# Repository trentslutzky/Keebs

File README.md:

# Keyboards

Custom split low-profile ergonomic keyboards

### Version 1

### Version 2

- in progress

https://github.com/daprice/keyswitches.pretty

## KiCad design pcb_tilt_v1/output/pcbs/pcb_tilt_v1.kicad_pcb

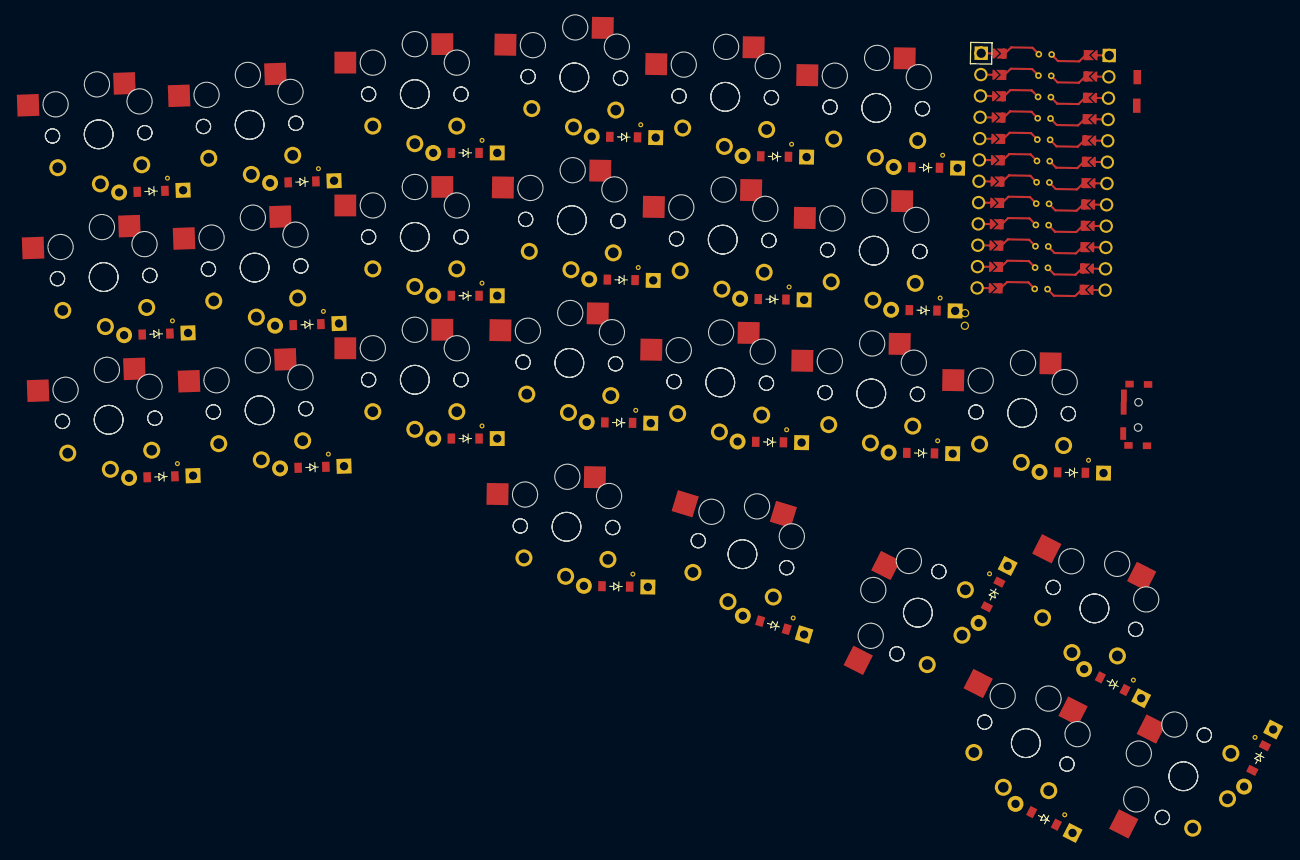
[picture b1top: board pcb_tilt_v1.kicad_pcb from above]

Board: 2 copper layers, 76 parts (0 on the bottom side), 36 nets, no tracks yet.

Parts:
D1, D2, D3, D4, D5, D6, D7, D8, D9, D10, D11, D12, D13, D14, D15, D16, D17, D18, D19, D20, D21, D22, D23, D24, D25: ComboDiode
MCU1: ProMicro
S1, S2, S3, S4, S5, S6, S7, S8, S9, S10, S11, S12, S13, S14, S15, S16, S17, S18, S19, S20, S21, S22, S23, S24, S25, S26, S27, S28, S29, S30, S31, S32, S33, S34, S35, S36, S37, S38, S39, S40, S41, S42, S43, S44, S45, S46, S47, S48, S49, S50: PG1350

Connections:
D2: D1.1, D1.2, S1.2, S2.2
D3: D2.1, D2.2, S3.2, S4.2
D4: D3.1, D3.2, S5.2, S6.2
D6: D4.1, D4.2, S7.2, S8.2
D7: D5.1, D5.2, S9.2, S10.2
D8: D6.1, D6.2, S11.2, S12.2
D10: D7.1, D7.2, S13.2, S14.2
D11: D8.1, D8.2, S15.2, S16.2
D12: D9.1, D9.2, S17.2, S18.2
D13: D10.1, D10.2, S19.2, S20.2
D14: D11.1, D11.2, S21.2, S22.2
D15: D12.1, D12.2, S23.2, S24.2
D16: D13.1, D13.2, S25.2, S26.2
D17: D14.1, D14.2, S27.2, S28.2
D18: D15.1, D15.2, S29.2, S30.2
D19: D16.1, D16.2, S31.2, S32.2
D20: D17.1, D17.2, S33.2, S34.2
D21: D18.1, D18.2, S35.2, S36.2
D22: D19.1, D19.2, S37.2, S38.2
D23: D20.1, D20.2, S39.2, S40.2
D24: D21.1, D21.2, S41.2, S42.2
D25: D23.1, D23.2, S45.2, S46.2
D26: D22.1, D22.2, S43.2, S44.2
D27: D24.1, D24.2, D25.1, D25.2, S47.2, S48.2, S49.2, S50.2
GND: MCU1.2, MCU1.21, MCU1.22
P0: MCU1.23, S3.1, S4.1, S9.1, S10.1, S15.1, S16.1, S23.1, S24.1, S31.1, S32.1, S37.1, S38.1, S45.1, S46.1
P1: MCU1.24, S5.1, S6.1, S11.1, S12.1, S17.1, S18.1, S25.1, S26.1, S33.1, S34.1, S39.1, S40.1, S49.1, S50.1
P2: MCU1.20, S1.1, S2.1, S7.1, S8.1, S13.1, S14.1, S21.1, S22.1, S29.1, S30.1, S35.1, S36.1, S43.1, S44.1
P3: MCU1.19, S19.1, S20.1, S27.1, S28.1, S41.1, S42.1, S47.1, S48.1
P4: D1.1, D1.2, D2.1, D2.2, D3.1, D3.2, MCU1.18
P5: D4.1, D4.2, D5.1, D5.2, D6.1, D6.2, MCU1.17
P6: D7.1, D7.2, D8.1, D8.2, D9.1, D9.2, MCU1.16
P7: D10.1, D10.2, D11.1, D11.2, D12.1, D12.2, D13.1, D13.2, MCU1.15
P8: D14.1, D14.2, D15.1, D15.2, D16.1, D16.2, D17.1, D17.2, MCU1.14
P9: D18.1, D18.2, D19.1, D19.2, D20.1, D20.2, D21.1, D21.2, MCU1.13
P10: D22.1, D22.2, D23.1, D23.2, D24.1, D24.2, D25.1, D25.2, MCU1.12

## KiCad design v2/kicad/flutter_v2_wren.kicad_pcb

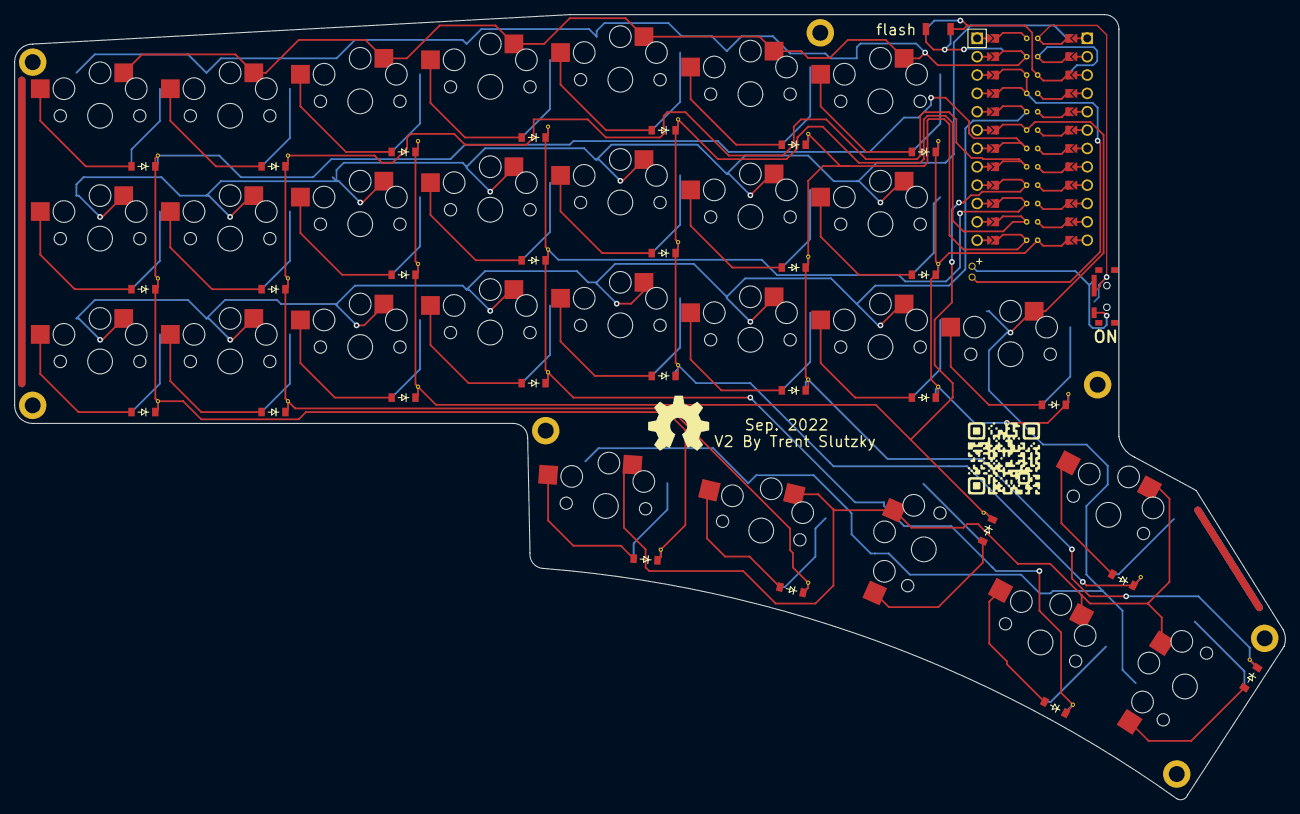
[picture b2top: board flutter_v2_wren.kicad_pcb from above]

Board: 2 copper layers, 175.9 x 108.6 mm, 57 parts (0 on the bottom side), 40 nets.

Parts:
D1, D2, D3, D4, D5, D6, D7, D8, D9, D10, D11, D12, D13, D14, D15, D16, D17, D18, D19, D20, D21, D22, D23, D24, D25, D26, D27, D28: ComboDiode
MCU1: ProMicro
S1, S2, S3, S4, S5, S6, S7, S8, S9, S10, S11, S12, S13, S14, S15, S16, S17, S18, S19, S20, S21, S22, S23, S24, S25, S26, S27, S28: PG1350

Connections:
D2: D3.2, S3.2
D3: D2.2, S2.2
D4: D1.2, S1.2
D5: D6.2, S6.2
D6: D5.2, S5.2
D7: D4.2, S4.2
D8: D9.2, S9.2
D9: D8.2, S8.2
D10: D7.2, S7.2
D11: D12.2, S12.2
D12: D11.2, S11.2
D13: D10.2, S10.2
D14: D15.2, S15.2
D15: D14.2, S14.2
D16: D13.2, S13.2
D17: D18.2, S18.2
D18: D17.2, S17.2
D19: D16.2, S16.2
D20: D21.2, S21.2
D21: D20.2, S20.2
D22: D19.2, S19.2
D23: D22.2, S22.2
D24: D24.2, S24.2
D25: D23.2, S23.2
D26: D25.2, S25.2
D27: D26.2, S26.2
D28: D27.2, S27.2
D29: D28.2, S28.2
GND: MCU1.2, MCU1.21, MCU1.22
P0: MCU1.23, S3.1, S6.1, S9.1, S12.1, S15.1, S18.1, S21.1
P1: MCU1.24, S2.1, S5.1, S8.1, S11.1, S14.1, S17.1, S20.1
P2: MCU1.20, S1.1, S4.1, S7.1, S10.1, S13.1, S16.1, S19.1
P3: MCU1.19, S22.1, S23.1, S24.1, S25.1, S26.1, S27.1, S28.1
P4: D1.1, D2.1, D3.1, D27.1, MCU1.18
P5: D4.1, D5.1, D6.1, D28.1, MCU1.17
P6: D7.1, D8.1, D9.1, D22.1, MCU1.16
P7: D10.1, D11.1, D12.1, D23.1, MCU1.15
P8: D13.1, D14.1, D15.1, D24.1, MCU1.14
P9: D16.1, D17.1, D18.1, D25.1, MCU1.13
P10: D19.1, D20.1, D21.1, D26.1, MCU1.12

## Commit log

2022-08-17 add v1 keeb
2022-09-13 update project/keyboard names
2022-09-13 add art
2022-09-13 update v1
2022-09-13 add ignore
2022-09-13 add ergogen reference and v2
2025-02-25 add ultra low profile keyboard
